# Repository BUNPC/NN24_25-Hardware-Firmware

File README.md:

This repository contains the technical documentation used to create all parts of the NN24 whole-head fNIRS system.

A description of the documents contained in this respository and other instructions related to the ninjaNIRS system can be found at openfnirs.org [here](https://openfnirs.org/hardware/ninjanirs2024/).

Please refer to the [ninjaNIRS Setup Guide](https://openfnirs.org/wp-content/uploads/2025/06/ninjaNIRS__Setup_Guide.pdf) when assembling your system for the first time to ensure proper configuration and operation.

Please use the [Hardware Forum](https://openfnirs.org/community/hardware-forum/) at openfnirs.org to discuss anything about the ninjaNIRS system.

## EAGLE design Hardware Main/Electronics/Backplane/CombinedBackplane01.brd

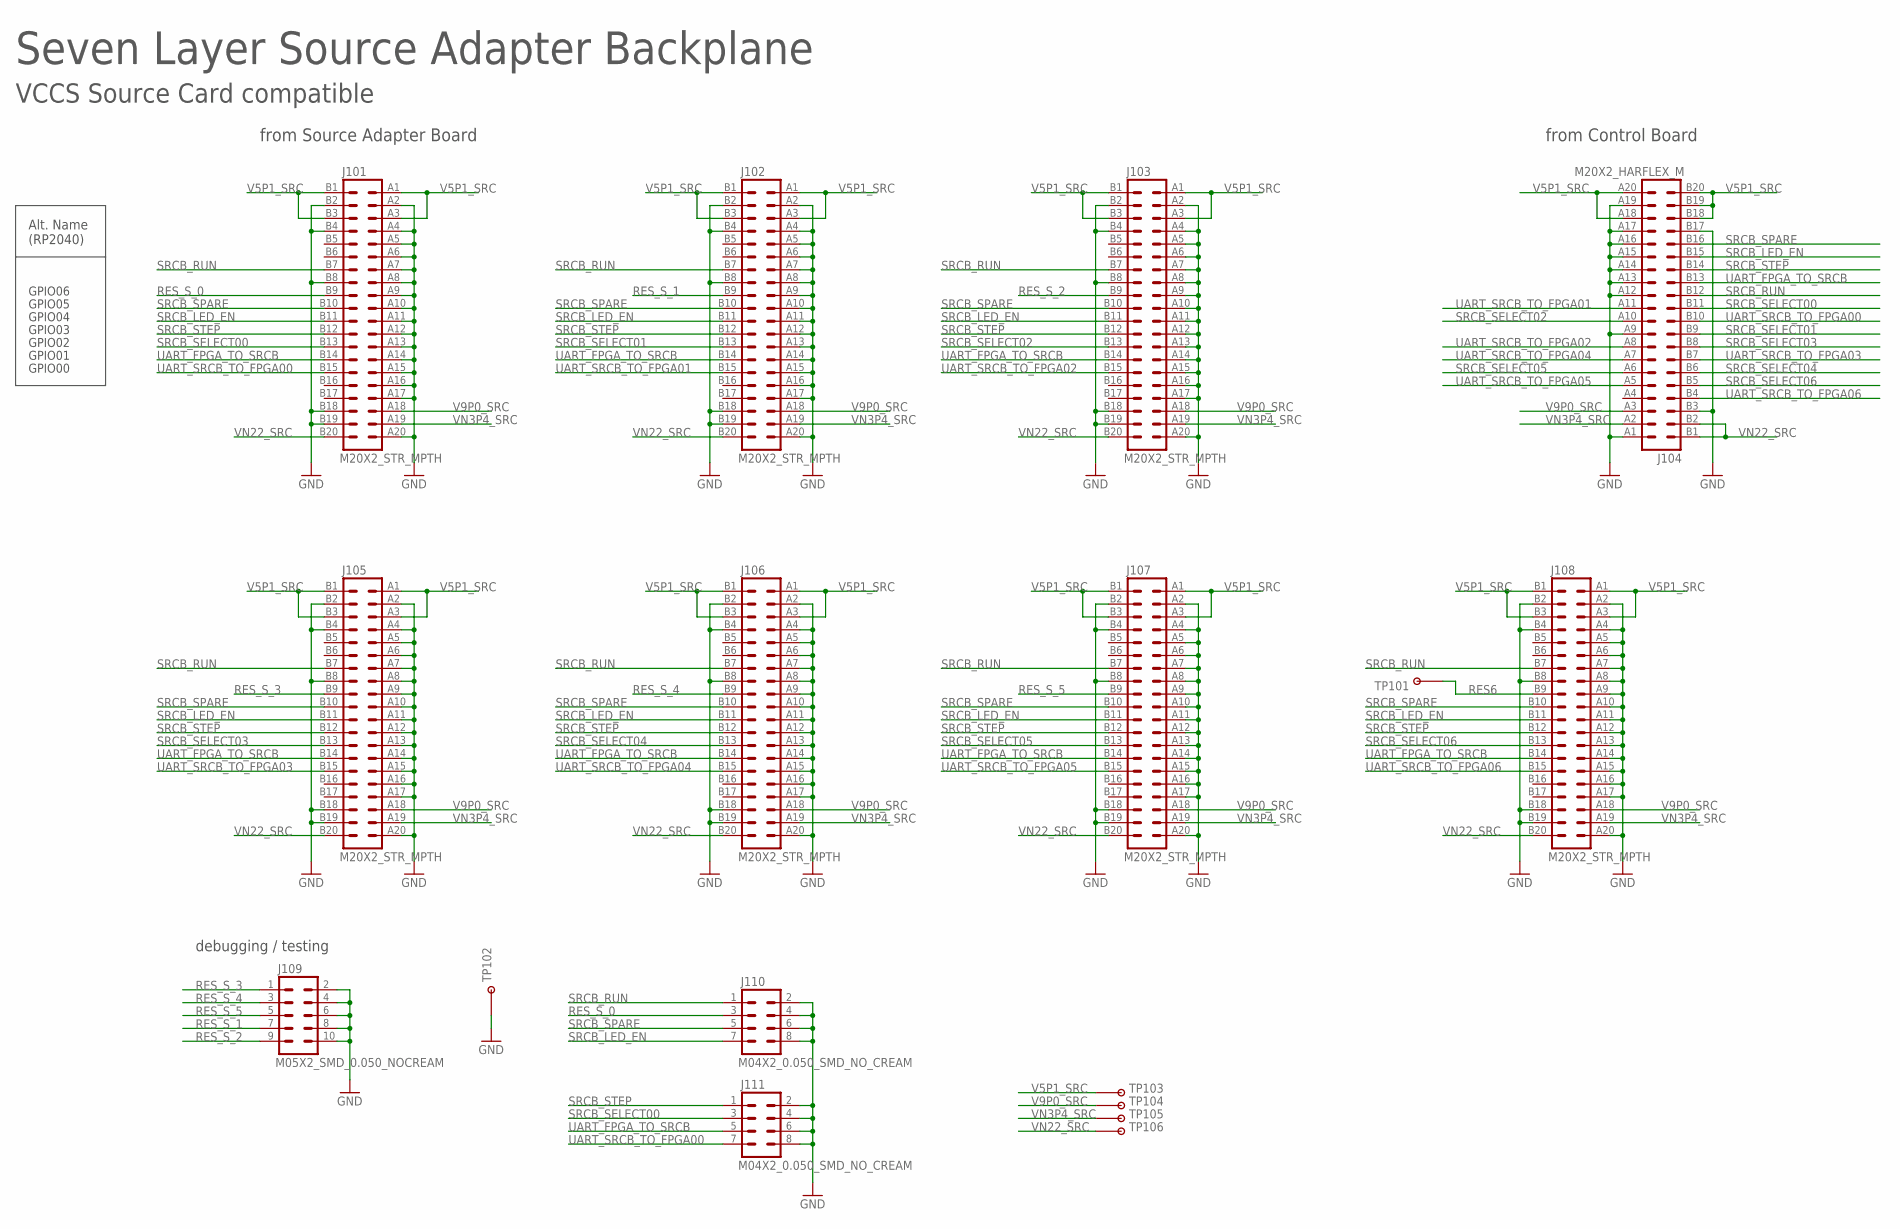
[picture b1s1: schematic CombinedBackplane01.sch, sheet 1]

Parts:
J101, J102, J103, J105, J106, J107, J108: M20X2_STR_MPTH; M20X2_HARFLEX_F_STR_MPTH
J104: M20X2_HARFLEX_M
J109: M05X2_SMD_0.050_NOCREAM; M05X2_0.050_SMD_NO_CREAM
J110, J111: M04X2_0.050_SMD_NO_CREAM
TP101, TP103, TP104, TP105, TP106: TESTPOINT_ROUND; TESTPAD_ROUND
TP102: TESTPOINTTUR; TURRET

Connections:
GND_SRC: J101.A2 (4), J101.A4 (8), J101.A5 (10), J101.A6 (12), J101.A7 (14), J101.A8 (16), J101.A9 (18), J101.A10 (20), J101.A11 (22), J101.A12 (24), J101.A13 (26), J101.A14 (28), J101.A15 (30), J101.A16 (32), J101.A17 (34), J101.A20 (40), J101.B2 (3), J101.B4 (7), J101.B8 (15), J101.B18 (35), J101.B19 (37), J102.A2 (4), J102.A4 (8), J102.A5 (10), J102.A6 (12), J102.A7 (14), J102.A8 (16), J102.A9 (18), J102.A10 (20), J102.A11 (22), J102.A12 (24), J102.A13 (26), J102.A14 (28), J102.A15 (30), J102.A16 (32), J102.A17 (34), J102.A20 (40), J102.B2 (3), J102.B4 (7), J102.B8 (15), J102.B18 (35), J102.B19 (37), J103.A2 (4), J103.A4 (8), J103.A5 (10), J103.A6 (12), J103.A7 (14), J103.A8 (16), J103.A9 (18), J103.A10 (20), J103.A11 (22), J103.A12 (24), J103.A13 (26), J103.A14 (28), J103.A15 (30), J103.A16 (32), J103.A17 (34), J103.A20 (40), J103.B2 (3), J103.B4 (7), J103.B8 (15), J103.B18 (35), J103.B19 (37), J104.A1 (2), J104.A9 (18), J104.A12 (24), J104.A13 (26), J104.A14 (28), J104.A15 (30), J104.A16 (32), J104.A17 (34), J104.A19 (38), J104.B3 (5), J104.B17 (33), J105.A2 (4), J105.A4 (8), J105.A5 (10), J105.A6 (12), J105.A7 (14), J105.A8 (16), J105.A9 (18), J105.A10 (20), J105.A11 (22), J105.A12 (24), J105.A13 (26), J105.A14 (28), J105.A15 (30), J105.A16 (32), J105.A17 (34), J105.A20 (40), J105.B2 (3), J105.B4 (7), J105.B8 (15), J105.B18 (35), J105.B19 (37), J106.A2 (4), J106.A4 (8), J106.A5 (10), J106.A6 (12), J106.A7 (14), J106.A8 (16), J106.A9 (18), J106.A10 (20), J106.A11 (22), J106.A12 (24), J106.A13 (26), J106.A14 (28), J106.A15 (30), J106.A16 (32), J106.A17 (34), J106.A20 (40), J106.B2 (3), J106.B4 (7), J106.B8 (15), J106.B18 (35), J106.B19 (37), J107.A2 (4), J107.A4 (8), J107.A5 (10), J107.A6 (12), J107.A7 (14), J107.A8 (16), J107.A9 (18), J107.A10 (20), J107.A11 (22), J107.A12 (24), J107.A13 (26), J107.A14 (28), J107.A15 (30), J107.A16 (32), J107.A17 (34), J107.A20 (40), J107.B2 (3), J107.B4 (7), J107.B8 (15), J107.B18 (35), J107.B19 (37), J108.A2 (4), J108.A4 (8), J108.A5 (10), J108.A6 (12), J108.A7 (14), J108.A8 (16), J108.A9 (18), J108.A10 (20), J108.A11 (22), J108.A12 (24), J108.A13 (26), J108.A14 (28), J108.A15 (30), J108.A16 (32), J108.A17 (34), J108.A20 (40), J108.B2 (3), J108.B4 (7), J108.B8 (15), J108.B18 (35), J108.B19 (37), J109.2, J109.4, J109.6, J109.8, J109.10, J110.2, J110.4, J110.6, J110.8, J111.2, J111.4, J111.6, J111.8, TP102.P$1
RES6: J108.B9 (17), TP101.P$1
RES_S_0: J101.B9 (17), J110.3
RES_S_1: J102.B9 (17), J109.7
RES_S_2: J103.B9 (17), J109.9
RES_S_3: J105.B9 (17), J109.1
RES_S_4: J106.B9 (17), J109.3
RES_S_5: J107.B9 (17), J109.5
SRCB_LED_EN: J101.B11 (21), J102.B11 (21), J103.B11 (21), J104.B15 (29), J105.B11 (21), J106.B11 (21), J107.B11 (21), J108.B11 (21), J110.7
SRCB_RUN: J101.B7 (13), J102.B7 (13), J103.B7 (13), J104.B12 (23), J105.B7 (13), J106.B7 (13), J107.B7 (13), J108.B7 (13), J110.1
SRCB_SELECT00: J101.B13 (25), J104.B11 (21), J111.3
SRCB_SELECT01: J102.B13 (25), J104.B9 (17)
SRCB_SELECT02: J103.B13 (25), J104.A10 (20)
SRCB_SELECT03: J104.B8 (15), J105.B13 (25)
SRCB_SELECT04: J104.B6 (11), J106.B13 (25)
SRCB_SELECT05: J104.A6 (12), J107.B13 (25)
SRCB_SELECT06: J104.B5 (9), J108.B13 (25)
SRCB_SPARE: J101.B10 (19), J102.B10 (19), J103.B10 (19), J104.B16 (31), J105.B10 (19), J106.B10 (19), J107.B10 (19), J108.B10 (19), J110.5
SRCB_STEP: J101.B12 (23), J102.B12 (23), J103.B12 (23), J104.B14 (27), J105.B12 (23), J106.B12 (23), J107.B12 (23), J108.B12 (23), J111.1
UART_FPGA_TO_SRCB: J101.B14 (27), J102.B14 (27), J103.B14 (27), J104.B13 (25), J105.B14 (27), J106.B14 (27), J107.B14 (27), J108.B14 (27), J111.5
UART_SRCB_TO_FPGA00: J101.B15 (29), J104.B10 (19), J111.7
UART_SRCB_TO_FPGA01: J102.B15 (29), J104.A11 (22)
UART_SRCB_TO_FPGA02: J103.B15 (29), J104.A8 (16)
UART_SRCB_TO_FPGA03: J104.B7 (13), J105.B15 (29)
UART_SRCB_TO_FPGA04: J104.A7 (14), J106.B15 (29)
UART_SRCB_TO_FPGA05: J104.A5 (10), J107.B15 (29)
UART_SRCB_TO_FPGA06: J104.B4 (7), J108.B15 (29)
V5P1_SRC: J101.A1 (2), J101.A3 (6), J101.B1 (1), J101.B3 (5), J102.A1 (2), J102.A3 (6), J102.B1 (1), J102.B3 (5), J103.A1 (2), J103.A3 (6), J103.B1 (1), J103.B3 (5), J104.A18 (36), J104.A20 (40), J104.B18 (35), J104.B19 (37), J104.B20 (39), J105.A1 (2), J105.A3 (6), J105.B1 (1), J105.B3 (5), J106.A1 (2), J106.A3 (6), J106.B1 (1), J106.B3 (5), J107.A1 (2), J107.A3 (6), J107.B1 (1), J107.B3 (5), J108.A1 (2), J108.A3 (6), J108.B1 (1), J108.B3 (5), TP103.P$1
V9P0_SRC: J101.A18 (36), J102.A18 (36), J103.A18 (36), J104.A3 (6), J105.A18 (36), J106.A18 (36), J107.A18 (36), J108.A18 (36), TP104.P$1
VN3P4_SRC: J101.A19 (38), J102.A19 (38), J103.A19 (38), J104.A2 (4), J105.A19 (38), J106.A19 (38), J107.A19 (38), J108.A19 (38), TP105.P$1
VN22_SRC: J101.B20 (39), J102.B20 (39), J103.B20 (39), J104.B1 (1), J104.B2 (3), J105.B20 (39), J106.B20 (39), J107.B20 (39), J108.B20 (39), TP106.P$1

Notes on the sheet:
Seven Layer Source Adapter Backplane
from Source Adapter Board
from Control Board
GPIO00
GPIO01
GPIO02
GPIO03
GPIO04
GPIO05
GPIO06
debugging / testing
Alt. Name (RP2040)
VCCS Source Card compatible

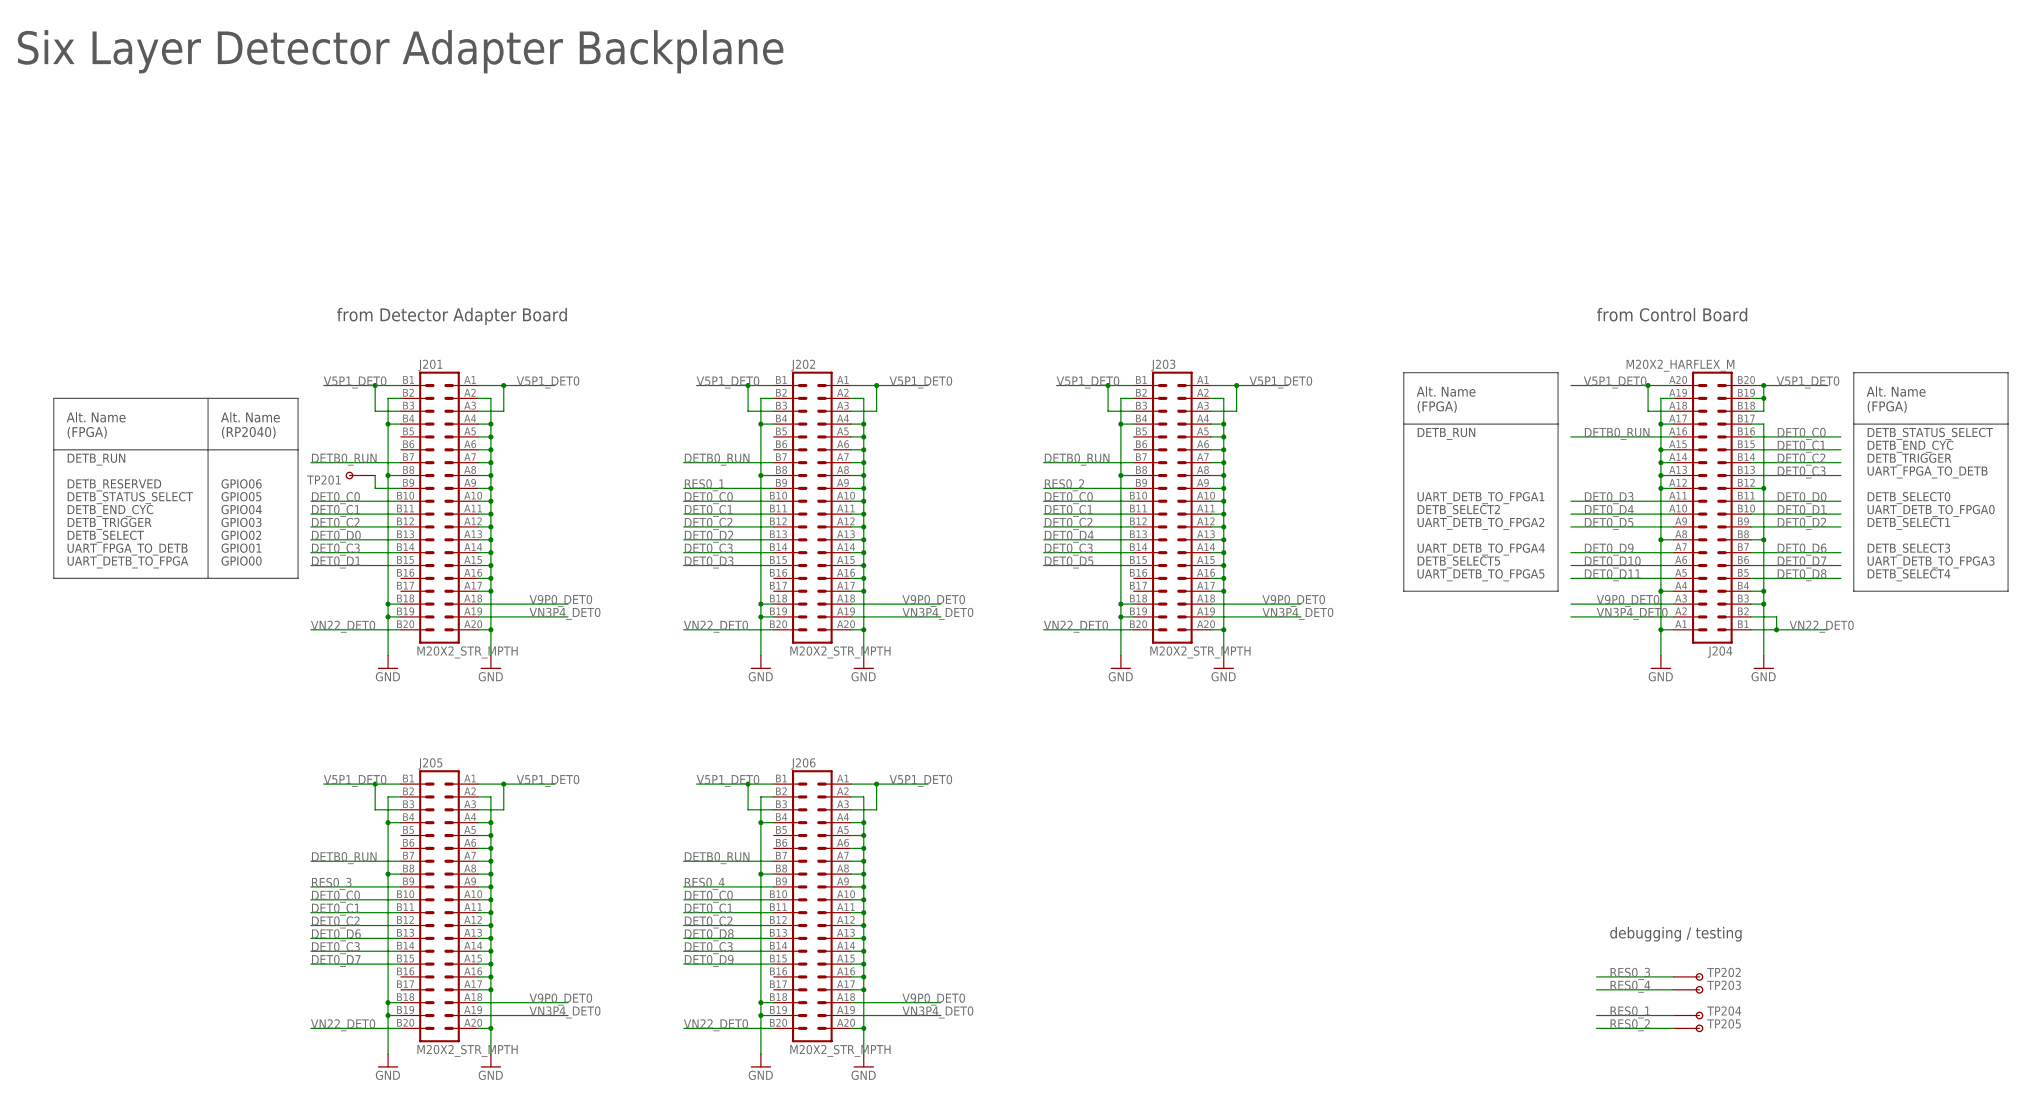
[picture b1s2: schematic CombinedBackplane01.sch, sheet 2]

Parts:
J201, J202, J203, J205, J206: M20X2_STR_MPTH; M20X2_HARFLEX_F_STR_MPTH
J204: M20X2_HARFLEX_M
TP201, TP202, TP203, TP204, TP205: TESTPOINT_ROUND; TESTPAD_ROUND

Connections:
DET0_C0: J201.B10 (19), J202.B10 (19), J203.B10 (19), J204.B16 (31), J205.B10 (19), J206.B10 (19)
DET0_C1: J201.B11 (21), J202.B11 (21), J203.B11 (21), J204.B15 (29), J205.B11 (21), J206.B11 (21)
DET0_C2: J201.B12 (23), J202.B12 (23), J203.B12 (23), J204.B14 (27), J205.B12 (23), J206.B12 (23)
DET0_C3: J201.B14 (27), J202.B14 (27), J203.B14 (27), J204.B13 (25), J205.B14 (27), J206.B14 (27)
DET0_D0: J201.B13 (25), J204.B11 (21)
DET0_D1: J201.B15 (29), J204.B10 (19)
DET0_D2: J202.B13 (25), J204.B9 (17)
DET0_D3: J202.B15 (29), J204.A11 (22)
DET0_D4: J203.B13 (25), J204.A10 (20)
DET0_D5: J203.B15 (29), J204.A9 (18)
DET0_D6: J204.B7 (13), J205.B13 (25)
DET0_D7: J204.B6 (11), J205.B15 (29)
DET0_D8: J204.B5 (9), J206.B13 (25)
DET0_D9: J204.A7 (14), J206.B15 (29)
DET0_D10: J204.A6 (12)
DET0_D11: J204.A5 (10)
DETB0_RUN: J201.B7 (13), J202.B7 (13), J203.B7 (13), J204.A16 (32), J205.B7 (13), J206.B7 (13)
GND: J201.A2 (4), J201.A4 (8), J201.A5 (10), J201.A6 (12), J201.A7 (14), J201.A8 (16), J201.A9 (18), J201.A10 (20), J201.A11 (22), J201.A12 (24), J201.A13 (26), J201.A14 (28), J201.A15 (30), J201.A16 (32), J201.A17 (34), J201.A20 (40), J201.B2 (3), J201.B4 (7), J201.B8 (15), J201.B18 (35), J201.B19 (37), J202.A2 (4), J202.A4 (8), J202.A5 (10), J202.A6 (12), J202.A7 (14), J202.A8 (16), J202.A9 (18), J202.A10 (20), J202.A11 (22), J202.A12 (24), J202.A13 (26), J202.A14 (28), J202.A15 (30), J202.A16 (32), J202.A17 (34), J202.A20 (40), J202.B2 (3), J202.B4 (7), J202.B8 (15), J202.B18 (35), J202.B19 (37), J203.A2 (4), J203.A4 (8), J203.A5 (10), J203.A6 (12), J203.A7 (14), J203.A8 (16), J203.A9 (18), J203.A10 (20), J203.A11 (22), J203.A12 (24), J203.A13 (26), J203.A14 (28), J203.A15 (30), J203.A16 (32), J203.A17 (34), J203.A20 (40), J203.B2 (3), J203.B4 (7), J203.B8 (15), J203.B18 (35), J203.B19 (37), J204.A1 (2), J204.A4 (8), J204.A8 (16), J204.A12 (24), J204.A13 (26), J204.A14 (28), J204.A15 (30), J204.A17 (34), J204.A19 (38), J204.B3 (5), J204.B4 (7), J204.B8 (15), J204.B12 (23), J204.B17 (33), J205.A2 (4), J205.A4 (8), J205.A5 (10), J205.A6 (12), J205.A7 (14), J205.A8 (16), J205.A9 (18), J205.A10 (20), J205.A11 (22), J205.A12 (24), J205.A13 (26), J205.A14 (28), J205.A15 (30), J205.A16 (32), J205.A17 (34), J205.A20 (40), J205.B2 (3), J205.B4 (7), J205.B8 (15), J205.B18 (35), J205.B19 (37), J206.A2 (4), J206.A4 (8), J206.A5 (10), J206.A6 (12), J206.A7 (14), J206.A8 (16), J206.A9 (18), J206.A10 (20), J206.A11 (22), J206.A12 (24), J206.A13 (26), J206.A14 (28), J206.A15 (30), J206.A16 (32), J206.A17 (34), J206.A20 (40), J206.B2 (3), J206.B4 (7), J206.B8 (15), J206.B18 (35), J206.B19 (37); also elsewhere on the board
unnamed: J201.B9 (17), TP201.P$1
RES0_1: J202.B9 (17), TP204.P$1
RES0_2: J203.B9 (17), TP205.P$1
RES0_3: J205.B9 (17), TP202.P$1
RES0_4: J206.B9 (17), TP203.P$1
V5P1_DET0: J201.A1 (2), J201.A3 (6), J201.B1 (1), J201.B3 (5), J202.A1 (2), J202.A3 (6), J202.B1 (1), J202.B3 (5), J203.A1 (2), J203.A3 (6), J203.B1 (1), J203.B3 (5), J204.A18 (36), J204.A20 (40), J204.B18 (35), J204.B19 (37), J204.B20 (39), J205.A1 (2), J205.A3 (6), J205.B1 (1), J205.B3 (5), J206.A1 (2), J206.A3 (6), J206.B1 (1), J206.B3 (5)
V9P0_DET0: J201.A18 (36), J202.A18 (36), J203.A18 (36), J204.A3 (6), J205.A18 (36), J206.A18 (36)
VN3P4_DET0: J201.A19 (38), J202.A19 (38), J203.A19 (38), J204.A2 (4), J205.A19 (38), J206.A19 (38)
VN22_DET0: J201.B20 (39), J202.B20 (39), J203.B20 (39), J204.B1 (1), J204.B2 (3), J205.B20 (39), J206.B20 (39)

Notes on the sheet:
Six Layer Detector Adapter Backplane
from Detector Adapter Board
from Control Board
GPIO00
GPIO01
GPIO02
GPIO03
GPIO04
GPIO05
GPIO06
UART_DETB_TO_FPGA
UART_FPGA_TO_DETB
DETB_SELECT
DETB_TRIGGER
DETB_END_CYC
DETB_STATUS_SELECT
DETB_RESERVED
DETB_RUN
debugging / testing
UART_DETB_TO_FPGA0
DETB_SELECT0
DETB_SELECT1
DETB_SELECT2
DETB_SELECT5
DETB_SELECT3
DETB_SELECT4
UART_DETB_TO_FPGA1
UART_DETB_TO_FPGA2
UART_DETB_TO_FPGA4
UART_DETB_TO_FPGA5
UART_DETB_TO_FPGA3
Alt. Name (FPGA)
Alt. Name (RP2040)

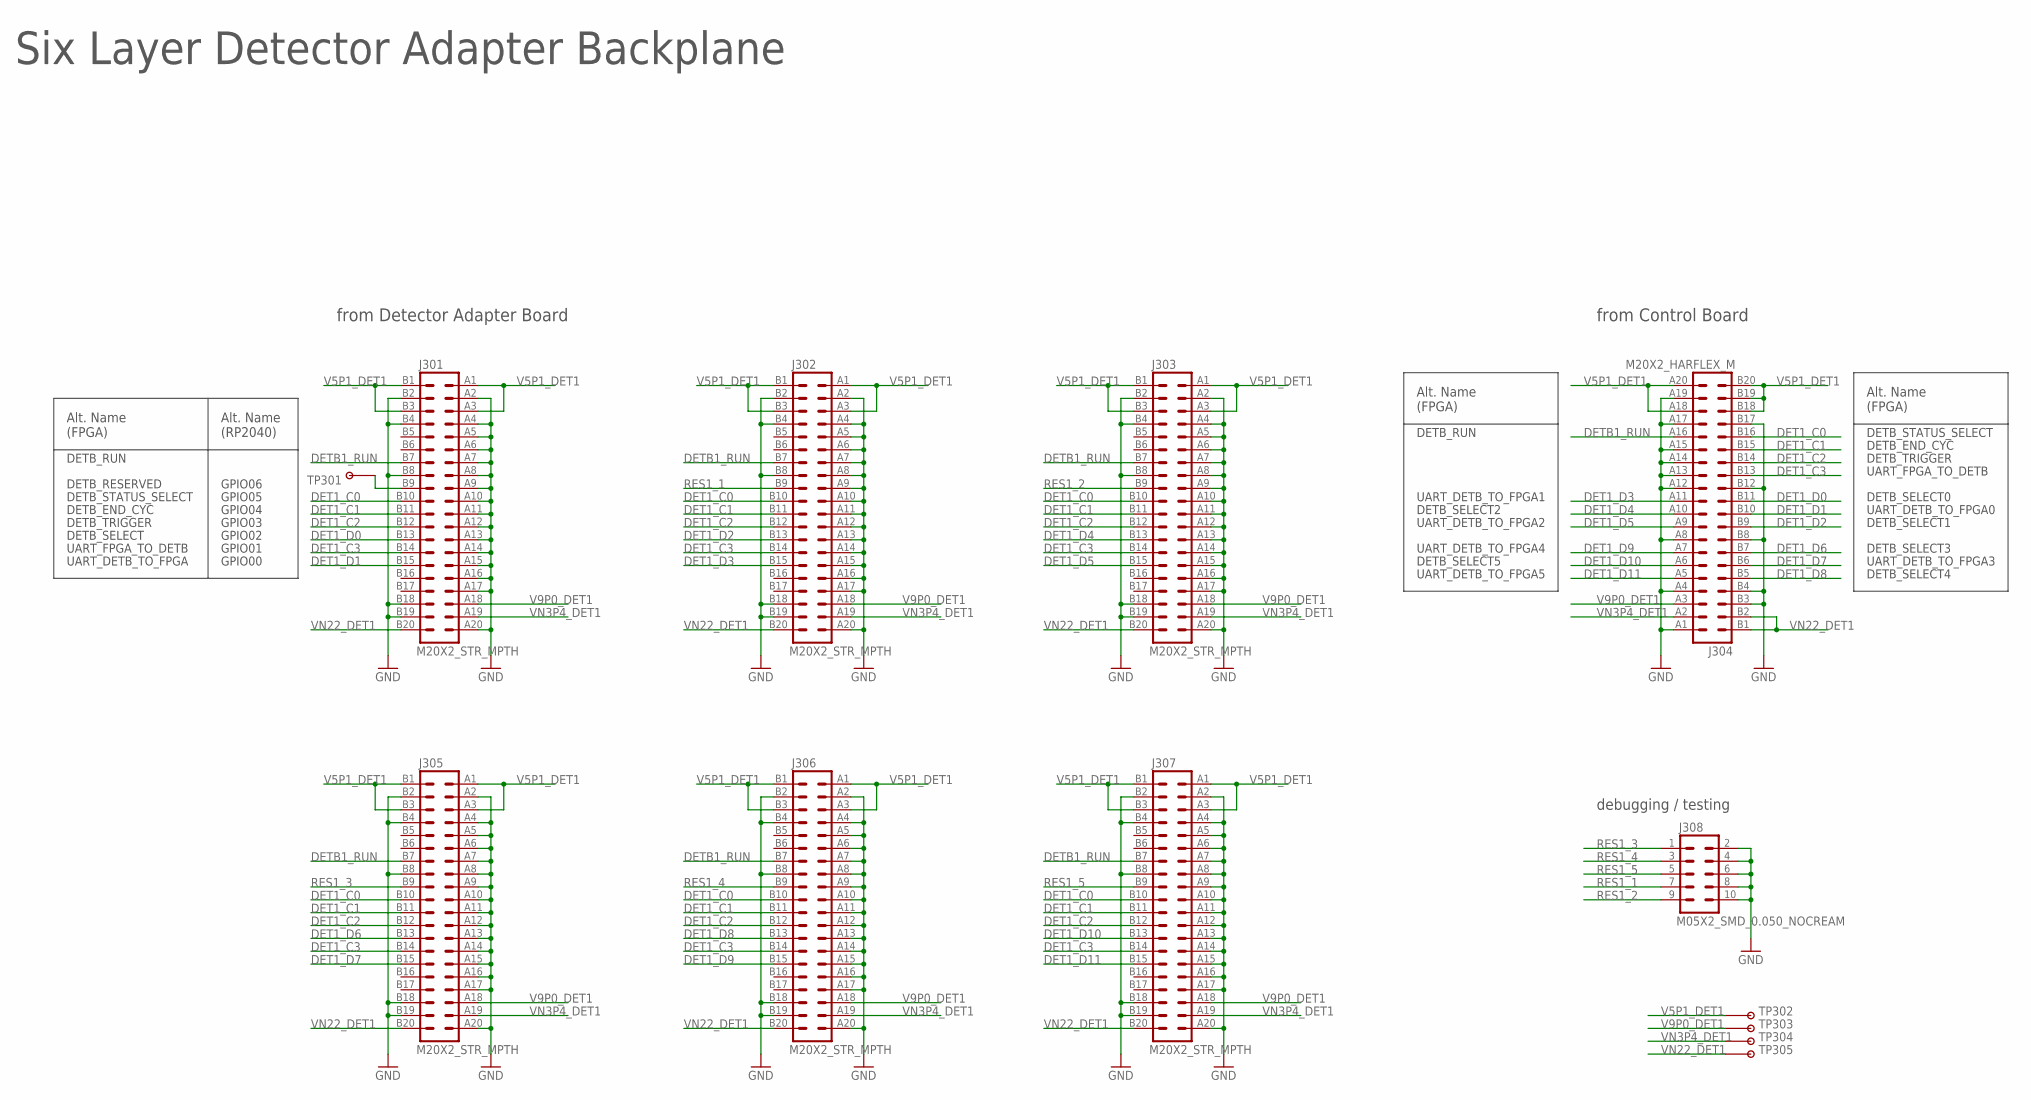
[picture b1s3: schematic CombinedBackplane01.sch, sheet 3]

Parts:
J301, J302, J303, J305, J306, J307: M20X2_STR_MPTH; M20X2_HARFLEX_F_STR_MPTH
J304: M20X2_HARFLEX_M
J308: M05X2_SMD_0.050_NOCREAM; M05X2_0.050_SMD_NO_CREAM
TP301, TP302, TP303, TP304, TP305: TESTPOINT_ROUND; TESTPAD_ROUND

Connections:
DET1_C0: J301.B10 (19), J302.B10 (19), J303.B10 (19), J304.B16 (31), J305.B10 (19), J306.B10 (19), J307.B10 (19)
DET1_C1: J301.B11 (21), J302.B11 (21), J303.B11 (21), J304.B15 (29), J305.B11 (21), J306.B11 (21), J307.B11 (21)
DET1_C2: J301.B12 (23), J302.B12 (23), J303.B12 (23), J304.B14 (27), J305.B12 (23), J306.B12 (23), J307.B12 (23)
DET1_C3: J301.B14 (27), J302.B14 (27), J303.B14 (27), J304.B13 (25), J305.B14 (27), J306.B14 (27), J307.B14 (27)
DET1_D0: J301.B13 (25), J304.B11 (21)
DET1_D1: J301.B15 (29), J304.B10 (19)
DET1_D2: J302.B13 (25), J304.B9 (17)
DET1_D3: J302.B15 (29), J304.A11 (22)
DET1_D4: J303.B13 (25), J304.A10 (20)
DET1_D5: J303.B15 (29), J304.A9 (18)
DET1_D6: J304.B7 (13), J305.B13 (25)
DET1_D7: J304.B6 (11), J305.B15 (29)
DET1_D8: J304.B5 (9), J306.B13 (25)
DET1_D9: J304.A7 (14), J306.B15 (29)
DET1_D10: J304.A6 (12), J307.B13 (25)
DET1_D11: J304.A5 (10), J307.B15 (29)
DETB1_RUN: J301.B7 (13), J302.B7 (13), J303.B7 (13), J304.A16 (32), J305.B7 (13), J306.B7 (13), J307.B7 (13)
GND: J301.A2 (4), J301.A4 (8), J301.A5 (10), J301.A6 (12), J301.A7 (14), J301.A8 (16), J301.A9 (18), J301.A10 (20), J301.A11 (22), J301.A12 (24), J301.A13 (26), J301.A14 (28), J301.A15 (30), J301.A16 (32), J301.A17 (34), J301.A20 (40), J301.B2 (3), J301.B4 (7), J301.B8 (15), J301.B18 (35), J301.B19 (37), J302.A2 (4), J302.A4 (8), J302.A5 (10), J302.A6 (12), J302.A7 (14), J302.A8 (16), J302.A9 (18), J302.A10 (20), J302.A11 (22), J302.A12 (24), J302.A13 (26), J302.A14 (28), J302.A15 (30), J302.A16 (32), J302.A17 (34), J302.A20 (40), J302.B2 (3), J302.B4 (7), J302.B8 (15), J302.B18 (35), J302.B19 (37), J303.A2 (4), J303.A4 (8), J303.A5 (10), J303.A6 (12), J303.A7 (14), J303.A8 (16), J303.A9 (18), J303.A10 (20), J303.A11 (22), J303.A12 (24), J303.A13 (26), J303.A14 (28), J303.A15 (30), J303.A16 (32), J303.A17 (34), J303.A20 (40), J303.B2 (3), J303.B4 (7), J303.B8 (15), J303.B18 (35), J303.B19 (37), J304.A1 (2), J304.A4 (8), J304.A8 (16), J304.A12 (24), J304.A13 (26), J304.A14 (28), J304.A15 (30), J304.A17 (34), J304.A19 (38), J304.B3 (5), J304.B4 (7), J304.B8 (15), J304.B12 (23), J304.B17 (33), J305.A2 (4), J305.A4 (8), J305.A5 (10), J305.A6 (12), J305.A7 (14), J305.A8 (16), J305.A9 (18), J305.A10 (20), J305.A11 (22), J305.A12 (24), J305.A13 (26), J305.A14 (28), J305.A15 (30), J305.A16 (32), J305.A17 (34), J305.A20 (40), J305.B2 (3), J305.B4 (7), J305.B8 (15), J305.B18 (35), J305.B19 (37), J306.A2 (4), J306.A4 (8), J306.A5 (10), J306.A6 (12), J306.A7 (14), J306.A8 (16), J306.A9 (18), J306.A10 (20), J306.A11 (22), J306.A12 (24), J306.A13 (26), J306.A14 (28), J306.A15 (30), J306.A16 (32), J306.A17 (34), J306.A20 (40), J306.B2 (3), J306.B4 (7), J306.B8 (15), J306.B18 (35), J306.B19 (37), J307.A2 (4), J307.A4 (8), J307.A5 (10), J307.A6 (12), J307.A7 (14), J307.A8 (16), J307.A9 (18), J307.A10 (20), J307.A11 (22), J307.A12 (24), J307.A13 (26), J307.A14 (28), J307.A15 (30), J307.A16 (32), J307.A17 (34), J307.A20 (40), J307.B2 (3), J307.B4 (7), J307.B8 (15), J307.B18 (35), J307.B19 (37), J308.2, J308.4, J308.6, J308.8, J308.10; also elsewhere on the board
unnamed: J301.B9 (17), TP301.P$1
RES1_1: J302.B9 (17), J308.7
RES1_2: J303.B9 (17), J308.9
RES1_3: J305.B9 (17), J308.1
RES1_4: J306.B9 (17), J308.3
RES1_5: J307.B9 (17), J308.5
V5P1_DET1: J301.A1 (2), J301.A3 (6), J301.B1 (1), J301.B3 (5), J302.A1 (2), J302.A3 (6), J302.B1 (1), J302.B3 (5), J303.A1 (2), J303.A3 (6), J303.B1 (1), J303.B3 (5), J304.A18 (36), J304.A20 (40), J304.B18 (35), J304.B19 (37), J304.B20 (39), J305.A1 (2), J305.A3 (6), J305.B1 (1), J305.B3 (5), J306.A1 (2), J306.A3 (6), J306.B1 (1), J306.B3 (5), J307.A1 (2), J307.A3 (6), J307.B1 (1), J307.B3 (5), TP302.P$1
V9P0_DET1: J301.A18 (36), J302.A18 (36), J303.A18 (36), J304.A3 (6), J305.A18 (36), J306.A18 (36), J307.A18 (36), TP303.P$1
VN3P4_DET1: J301.A19 (38), J302.A19 (38), J303.A19 (38), J304.A2 (4), J305.A19 (38), J306.A19 (38), J307.A19 (38), TP304.P$1
VN22_DET1: J301.B20 (39), J302.B20 (39), J303.B20 (39), J304.B1 (1), J304.B2 (3), J305.B20 (39), J306.B20 (39), J307.B20 (39), TP305.P$1

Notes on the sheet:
Six Layer Detector Adapter Backplane
from Detector Adapter Board
from Control Board
GPIO00
GPIO01
GPIO02
GPIO03
GPIO04
GPIO05
GPIO06
UART_DETB_TO_FPGA
UART_FPGA_TO_DETB
DETB_SELECT
DETB_TRIGGER
DETB_END_CYC
DETB_STATUS_SELECT
DETB_RESERVED
DETB_RUN
debugging / testing
UART_DETB_TO_FPGA0
DETB_SELECT0
DETB_SELECT1
DETB_SELECT2
DETB_SELECT5
DETB_SELECT3
DETB_SELECT4
UART_DETB_TO_FPGA1
UART_DETB_TO_FPGA2
UART_DETB_TO_FPGA4
UART_DETB_TO_FPGA5
UART_DETB_TO_FPGA3
Alt. Name (FPGA)
Alt. Name (RP2040)

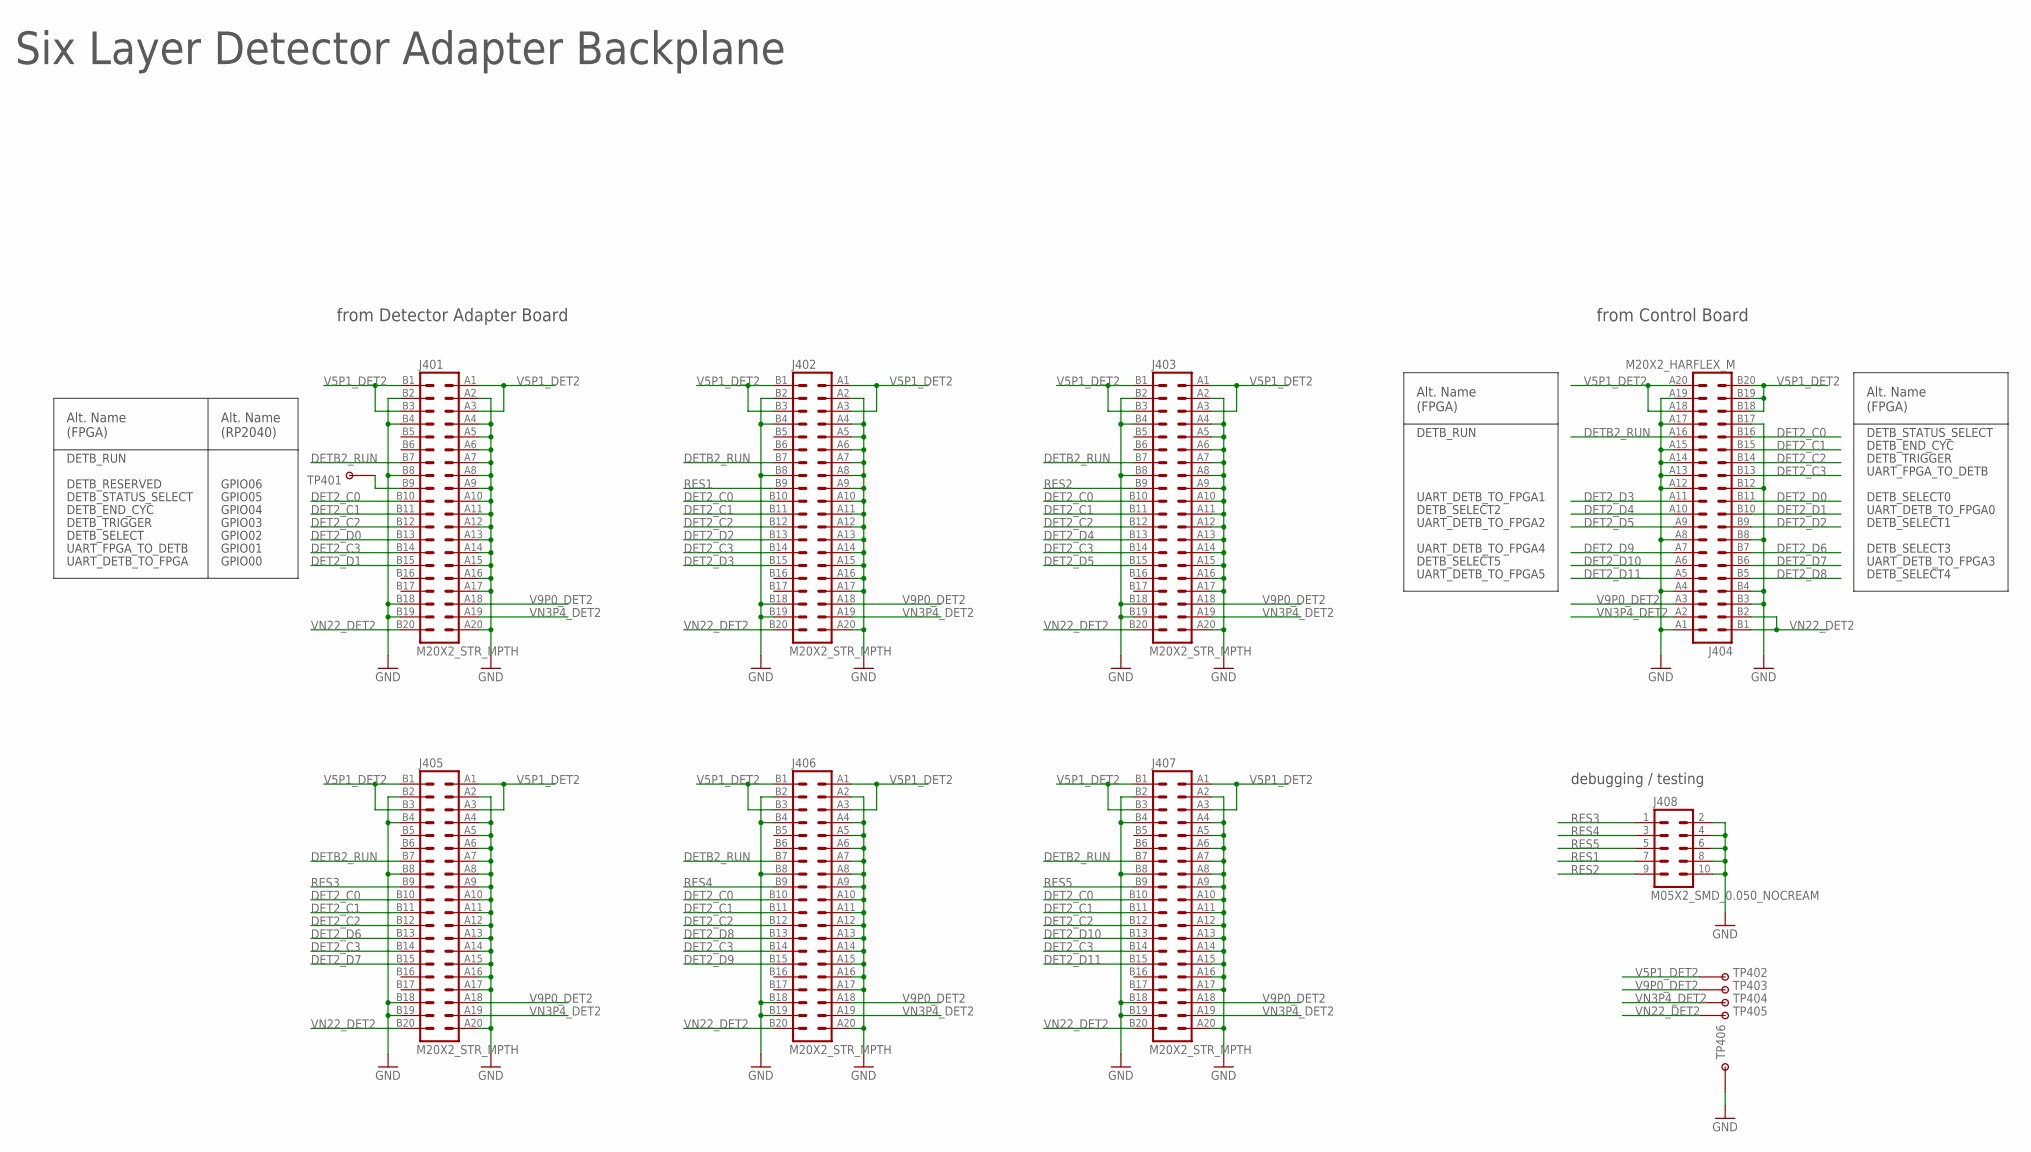
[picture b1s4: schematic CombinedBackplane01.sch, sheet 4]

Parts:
J401, J402, J403, J405, J406, J407: M20X2_STR_MPTH; M20X2_HARFLEX_F_STR_MPTH
J404: M20X2_HARFLEX_M
J408: M05X2_SMD_0.050_NOCREAM; M05X2_0.050_SMD_NO_CREAM
TP401, TP402, TP403, TP404, TP405: TESTPOINT_ROUND; TESTPAD_ROUND
TP406: TESTPOINTTUR; TURRET

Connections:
DET2_C0: J401.B10 (19), J402.B10 (19), J403.B10 (19), J404.B16 (31), J405.B10 (19), J406.B10 (19), J407.B10 (19)
DET2_C1: J401.B11 (21), J402.B11 (21), J403.B11 (21), J404.B15 (29), J405.B11 (21), J406.B11 (21), J407.B11 (21)
DET2_C2: J401.B12 (23), J402.B12 (23), J403.B12 (23), J404.B14 (27), J405.B12 (23), J406.B12 (23), J407.B12 (23)
DET2_C3: J401.B14 (27), J402.B14 (27), J403.B14 (27), J404.B13 (25), J405.B14 (27), J406.B14 (27), J407.B14 (27)
DET2_D0: J401.B13 (25), J404.B11 (21)
DET2_D1: J401.B15 (29), J404.B10 (19)
DET2_D2: J402.B13 (25), J404.B9 (17)
DET2_D3: J402.B15 (29), J404.A11 (22)
DET2_D4: J403.B13 (25), J404.A10 (20)
DET2_D5: J403.B15 (29), J404.A9 (18)
DET2_D6: J404.B7 (13), J405.B13 (25)
DET2_D7: J404.B6 (11), J405.B15 (29)
DET2_D8: J404.B5 (9), J406.B13 (25)
DET2_D9: J404.A7 (14), J406.B15 (29)
DET2_D10: J404.A6 (12), J407.B13 (25)
DET2_D11: J404.A5 (10), J407.B15 (29)
DETB2_RUN: J401.B7 (13), J402.B7 (13), J403.B7 (13), J404.A16 (32), J405.B7 (13), J406.B7 (13), J407.B7 (13)
GND: J401.A2 (4), J401.A4 (8), J401.A5 (10), J401.A6 (12), J401.A7 (14), J401.A8 (16), J401.A9 (18), J401.A10 (20), J401.A11 (22), J401.A12 (24), J401.A13 (26), J401.A14 (28), J401.A15 (30), J401.A16 (32), J401.A17 (34), J401.A20 (40), J401.B2 (3), J401.B4 (7), J401.B8 (15), J401.B18 (35), J401.B19 (37), J402.A2 (4), J402.A4 (8), J402.A5 (10), J402.A6 (12), J402.A7 (14), J402.A8 (16), J402.A9 (18), J402.A10 (20), J402.A11 (22), J402.A12 (24), J402.A13 (26), J402.A14 (28), J402.A15 (30), J402.A16 (32), J402.A17 (34), J402.A20 (40), J402.B2 (3), J402.B4 (7), J402.B8 (15), J402.B18 (35), J402.B19 (37), J403.A2 (4), J403.A4 (8), J403.A5 (10), J403.A6 (12), J403.A7 (14), J403.A8 (16), J403.A9 (18), J403.A10 (20), J403.A11 (22), J403.A12 (24), J403.A13 (26), J403.A14 (28), J403.A15 (30), J403.A16 (32), J403.A17 (34), J403.A20 (40), J403.B2 (3), J403.B4 (7), J403.B8 (15), J403.B18 (35), J403.B19 (37), J404.A1 (2), J404.A4 (8), J404.A8 (16), J404.A12 (24), J404.A13 (26), J404.A14 (28), J404.A15 (30), J404.A17 (34), J404.A19 (38), J404.B3 (5), J404.B4 (7), J404.B8 (15), J404.B12 (23), J404.B17 (33), J405.A2 (4), J405.A4 (8), J405.A5 (10), J405.A6 (12), J405.A7 (14), J405.A8 (16), J405.A9 (18), J405.A10 (20), J405.A11 (22), J405.A12 (24), J405.A13 (26), J405.A14 (28), J405.A15 (30), J405.A16 (32), J405.A17 (34), J405.A20 (40), J405.B2 (3), J405.B4 (7), J405.B8 (15), J405.B18 (35), J405.B19 (37), J406.A2 (4), J406.A4 (8), J406.A5 (10), J406.A6 (12), J406.A7 (14), J406.A8 (16), J406.A9 (18), J406.A10 (20), J406.A11 (22), J406.A12 (24), J406.A13 (26), J406.A14 (28), J406.A15 (30), J406.A16 (32), J406.A17 (34), J406.A20 (40), J406.B2 (3), J406.B4 (7), J406.B8 (15), J406.B18 (35), J406.B19 (37), J407.A2 (4), J407.A4 (8), J407.A5 (10), J407.A6 (12), J407.A7 (14), J407.A8 (16), J407.A9 (18), J407.A10 (20), J407.A11 (22), J407.A12 (24), J407.A13 (26), J407.A14 (28), J407.A15 (30), J407.A16 (32), J407.A17 (34), J407.A20 (40), J407.B2 (3), J407.B4 (7), J407.B8 (15), J407.B18 (35), J407.B19 (37), J408.2, J408.4, J408.6, J408.8, J408.10, TP406.P$1; also elsewhere on the board
unnamed: J401.B9 (17), TP401.P$1
RES1: J402.B9 (17), J408.7
RES2: J403.B9 (17), J408.9
RES3: J405.B9 (17), J408.1
RES4: J406.B9 (17), J408.3
RES5: J407.B9 (17), J408.5
V5P1_DET2: J401.A1 (2), J401.A3 (6), J401.B1 (1), J401.B3 (5), J402.A1 (2), J402.A3 (6), J402.B1 (1), J402.B3 (5), J403.A1 (2), J403.A3 (6), J403.B1 (1), J403.B3 (5), J404.A18 (36), J404.A20 (40), J404.B18 (35), J404.B19 (37), J404.B20 (39), J405.A1 (2), J405.A3 (6), J405.B1 (1), J405.B3 (5), J406.A1 (2), J406.A3 (6), J406.B1 (1), J406.B3 (5), J407.A1 (2), J407.A3 (6), J407.B1 (1), J407.B3 (5), TP402.P$1
V9P0_DET2: J401.A18 (36), J402.A18 (36), J403.A18 (36), J404.A3 (6), J405.A18 (36), J406.A18 (36), J407.A18 (36), TP403.P$1
VN3P4_DET2: J401.A19 (38), J402.A19 (38), J403.A19 (38), J404.A2 (4), J405.A19 (38), J406.A19 (38), J407.A19 (38), TP404.P$1
VN22_DET2: J401.B20 (39), J402.B20 (39), J403.B20 (39), J404.B1 (1), J404.B2 (3), J405.B20 (39), J406.B20 (39), J407.B20 (39), TP405.P$1

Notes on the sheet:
Six Layer Detector Adapter Backplane
from Detector Adapter Board
from Control Board
GPIO00
GPIO01
GPIO02
GPIO03
GPIO04
GPIO05
GPIO06
UART_DETB_TO_FPGA
UART_FPGA_TO_DETB
DETB_SELECT
DETB_TRIGGER
DETB_END_CYC
DETB_STATUS_SELECT
DETB_RESERVED
DETB_RUN
debugging / testing
UART_DETB_TO_FPGA0
DETB_SELECT0
DETB_SELECT1
DETB_SELECT2
DETB_SELECT5
DETB_SELECT3
DETB_SELECT4
UART_DETB_TO_FPGA1
UART_DETB_TO_FPGA2
UART_DETB_TO_FPGA4
UART_DETB_TO_FPGA5
UART_DETB_TO_FPGA3
Alt. Name (FPGA)
Alt. Name (RP2040)
